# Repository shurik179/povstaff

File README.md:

# POV staff
This repository contains all files related to Persistence of Vision (POV) staff project. A detailed write-up of Version 1 of this project is available on  Instructables at [https://www.instructables.com/Persistence-of-Vision-LED-Staff/](https://www.instructables.com/Persistence-of-Vision-LED-Staff/); you can also find there photos  of the staff in action.

The latest version (as of June 1, 2023) is 4.1. It is documented at
https://povstaff.readthedocs.io

## Structure of this repository  
This repository is organized as follows:

* `docs`: documentation
* `code`: this directory contains the source code for the staff software
* `hardware`:  design files for the custom PCBs used in
  the project, as well as STEP files for the 3d printed components.
* `images`: sample image(s) and  `imagelist.txt` file

## Authors and license
This project was created by Alexander Kirillov <irobotics.store@gmail.com>; it is
based on [earlier work](https://learn.adafruit.com/pov-dotstar-double-staff) of
Phillip Burgess and Erin St Blaine from Adafruit. The project is available under
MIT license; see LICENSE file for details.

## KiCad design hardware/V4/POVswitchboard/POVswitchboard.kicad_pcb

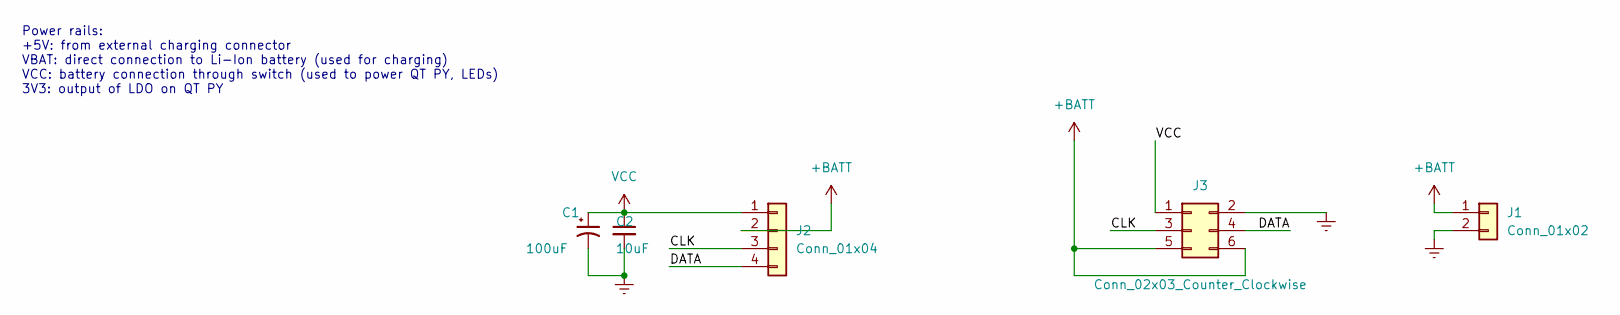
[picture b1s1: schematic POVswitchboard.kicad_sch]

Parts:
C1: 100uF; CP_Radial_D6.3mm_P2.50mm
C2: 10uF; C_0805_2012Metric; LCSC C15850
J1: Conn_01x02; JST_XH_B2B-XH-A_1x02_P2.50mm_Vertical
J2: Conn_01x04; connector-4p-large-nosilk
J3: Conn_02x03_Counter_Clockwise; PinSocket_2x03_P2.54mm_Horizontal

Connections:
+BATT: J1.1, J2.2, J3.5, J3.6
/CLK: J2.3, J3.3
/DATA: J2.4, J3.4
GNDREF: C1.2, C2.2, J1.2, J3.2
VCC: C1.1, C2.1, J2.1, J3.1

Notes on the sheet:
Power rails: +5V: from external charging connector VBAT: direct connection to Li-Ion battery (used for charging) VCC: battery connection through switch (used to power QT PY, LEDs) 3V3: output of LDO on QT PY

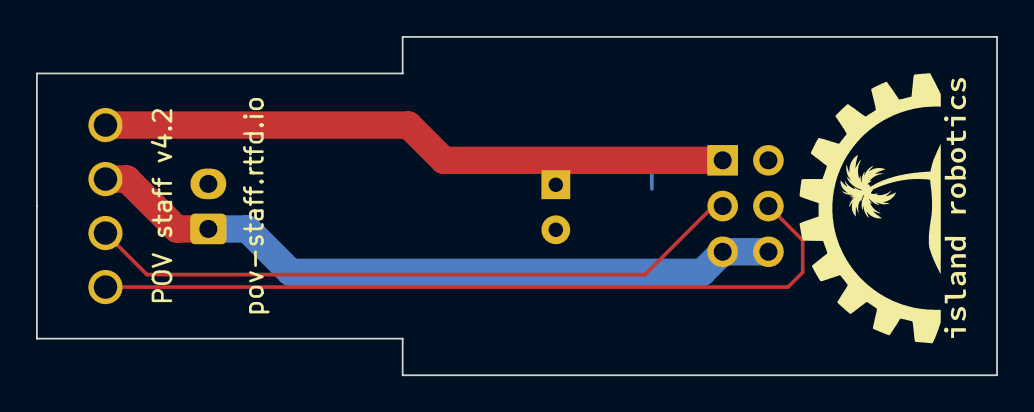
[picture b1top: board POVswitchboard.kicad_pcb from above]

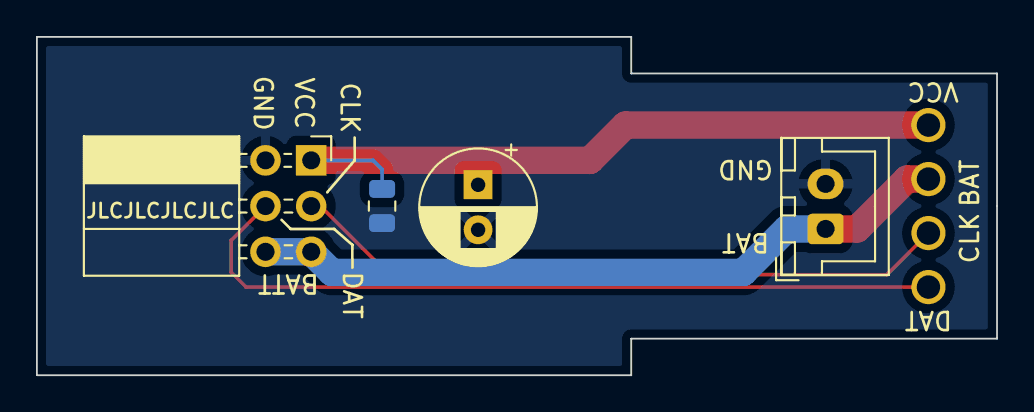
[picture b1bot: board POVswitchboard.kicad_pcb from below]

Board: 2 copper layers, 53.3 x 18.8 mm, 5 parts (4 on the bottom side), 5 nets.

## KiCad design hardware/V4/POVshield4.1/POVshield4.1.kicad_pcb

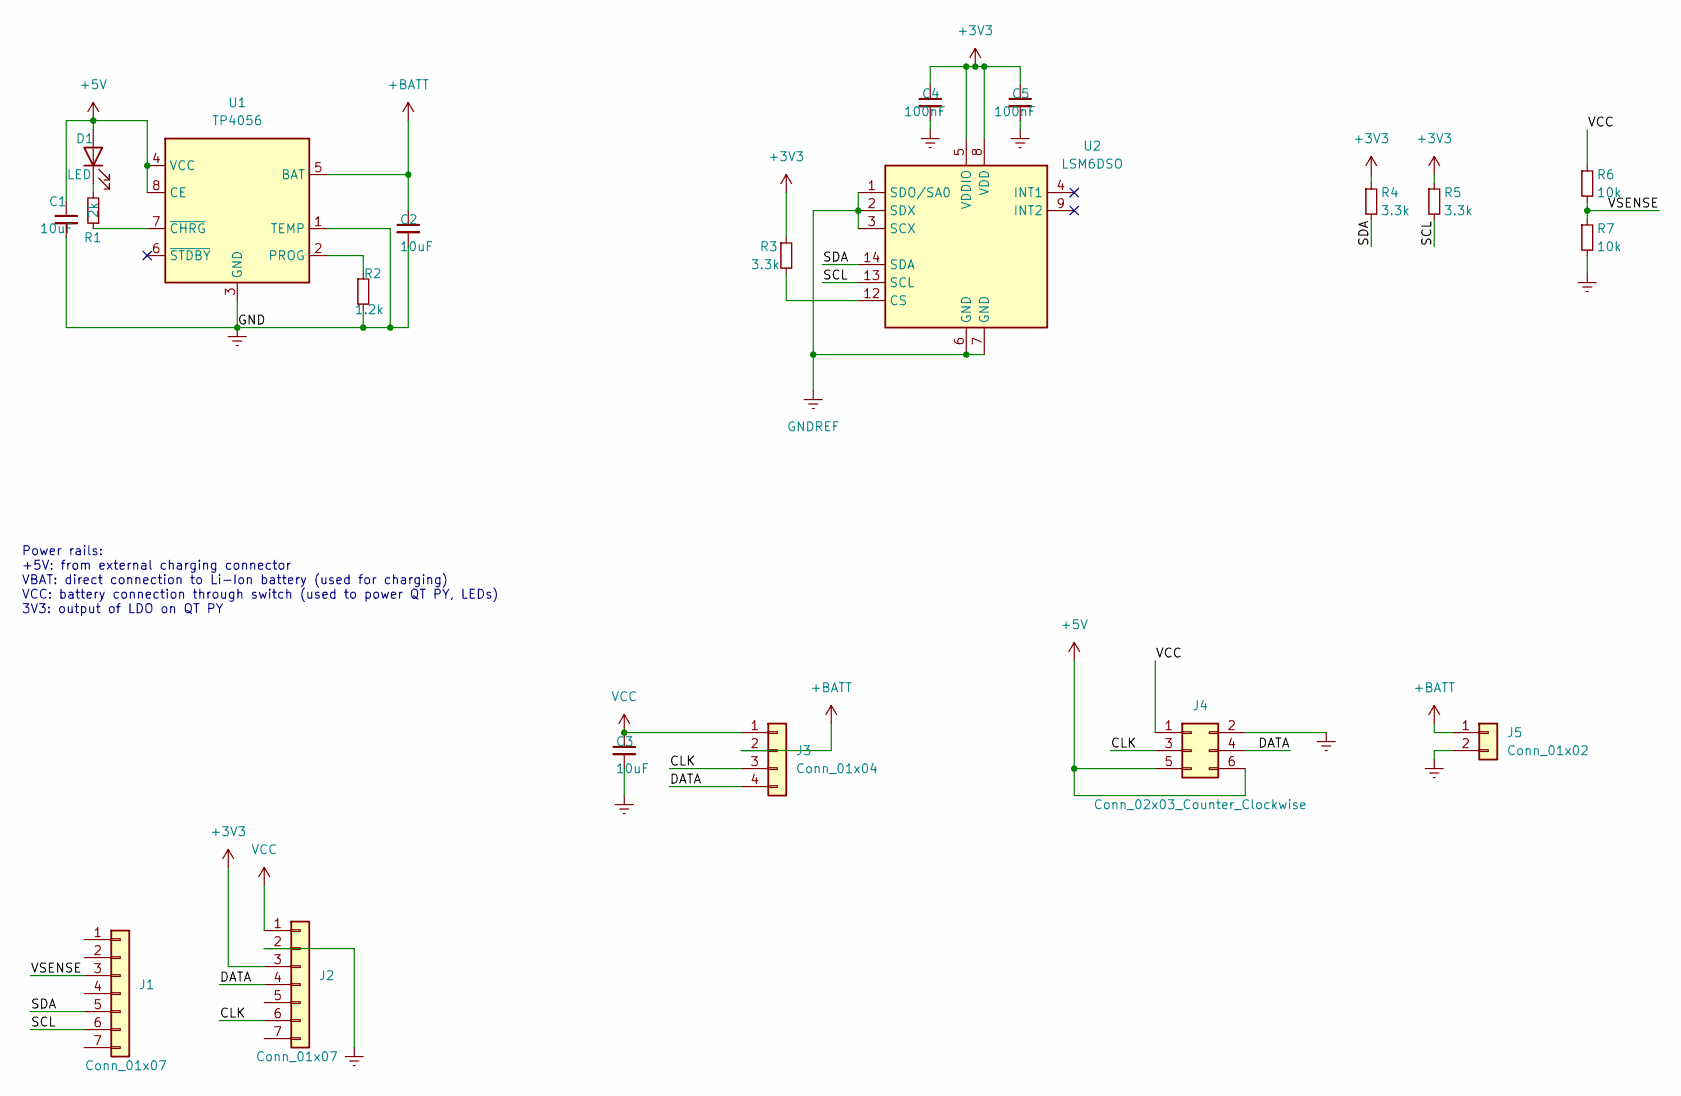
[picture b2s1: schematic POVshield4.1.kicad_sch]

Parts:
C1, C2, C3: 10uF; C_0805_2012Metric; LCSC C15850
C4, C5: 100nF; C_0603_1608Metric; LCSC C14663
D1: LED; LED_0603_1608Metric; LCSC C72038
J1, J2: Conn_01x07; PinSocket_1x07_P2.54mm_Vertical
J3: Conn_01x04; connector-4p-large-nosilk
J4: Conn_02x03_Counter_Clockwise; PinSocket_2x03_P2.54mm_Horizontal
J5: Conn_01x02; JST_XH_B2B-XH-A_1x02_P2.50mm_Vertical
R1: 2k; R_0603_1608Metric; LCSC C22975
R2: 1.2k; R_0603_1608Metric; LCSC C22765
R3, R4, R5: 3.3k; R_0603_1608Metric; LCSC C22978
R6, R7: 10k; R_0603_1608Metric; LCSC C25804
U1: TP4056; HSOP-8-1EP_3.9x4.9mm_P1.27mm_EP2.41x3.1mm_ThermalVias; LCSC C16581
U2: LSM6DSO; Bosch_LGA-14_3x2.5mm_P0.5mm

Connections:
+3V3: C4.1, C5.1, J2.3, R3.1, R4.1, R5.1, U2.5 (VDDIO), U2.8 (VDD)
+5V: C1.1, D1.2 (A), J4.5, J4.6, U1.4 (VCC), U1.8 (CE)
+BATT: C2.1, J3.2, J5.1, U1.5 (BAT)
/CLK: J2.6, J3.3, J4.3
/DATA: J2.4, J3.4, J4.4
/SCL: J1.6, R5.2, U2.13 (SCL)
/SDA: J1.5, R4.2, U2.14 (SDA)
/VSENSE: J1.3, R6.2, R7.1
EP: C1.2, C2.2, C3.2, C4.2, C5.2, J2.2, J4.2, J5.2, R2.2, R7.2, U1.1 (TEMP), U1.3 (GND), U1.9 (EP), U2.1 (SDO/SA0), U2.2 (SDX), U2.3 (SCX), U2.6 (GND), U2.7 (GND)
unnamed: D1.1 (K), R1.2
unnamed: R1.1, U1.7 (~CHRG)
unnamed: R2.1, U1.2 (PROG)
unnamed: R3.2, U2.12 (CS)
VCC: C3.1, J2.1, J3.1, J4.1, R6.1

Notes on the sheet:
Power rails: +5V: from external charging connector VBAT: direct connection to Li-Ion battery (used for charging) VCC: battery connection through switch (used to power QT PY, LEDs) 3V3: output of LDO on QT PY

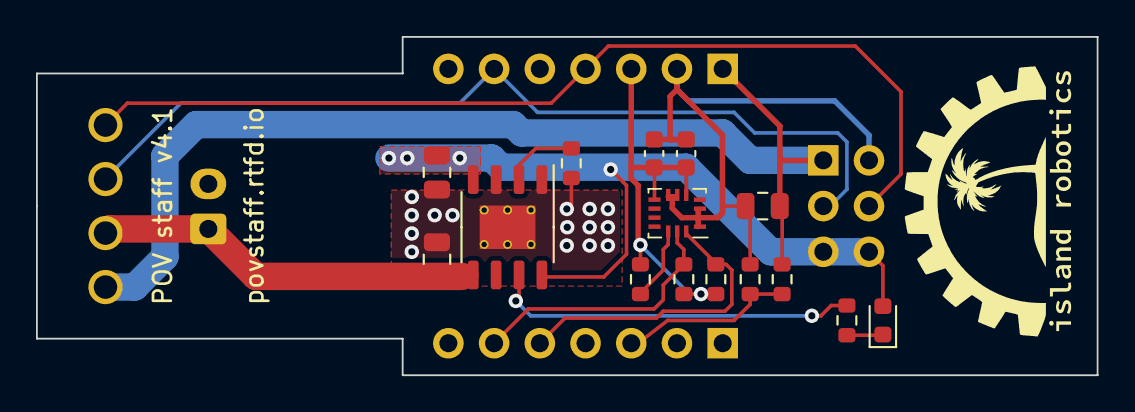
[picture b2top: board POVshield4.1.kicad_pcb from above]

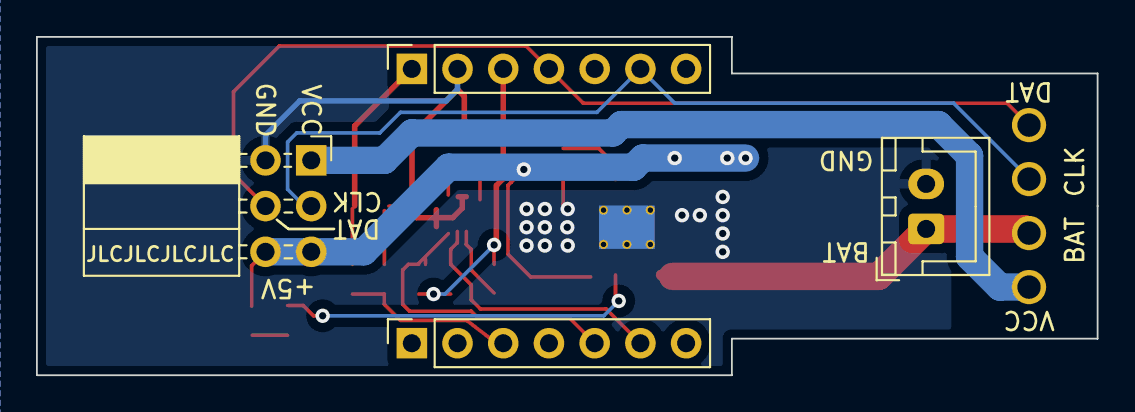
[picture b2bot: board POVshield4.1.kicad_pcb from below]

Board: 2 copper layers, 58.9 x 18.8 mm, 20 parts (4 on the bottom side), 14 nets.

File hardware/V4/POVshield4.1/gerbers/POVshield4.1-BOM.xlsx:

Designator | Footprint | Comment | JLCPCB Part #（optional）
C1,C2,C3 | C_0805_2012Metric | 10uF | C15850
C4,C5 | C_0603_1608Metric | 100nF | C14663
D1 | LED_0603_1608Metric | LED | C72038
R1 | R_0603_1608Metric | 2k | C22975
R2 | R_0603_1608Metric | 1.2k | C22765
R3,R4,R5 | R_0603_1608Metric | 3.3k | C22978
R6,R7 | R_0603_1608Metric | 10k | C25804
U2 | Bosch_LGA-14_3x2.5mm_P0.5mm | LSM6DSO | C2829074
U1 | HSOP-8-1EP_3.9x4.9mm_P1.27mm_EP2.41x3.1mm_ThermalVias | TP4056 | C16581

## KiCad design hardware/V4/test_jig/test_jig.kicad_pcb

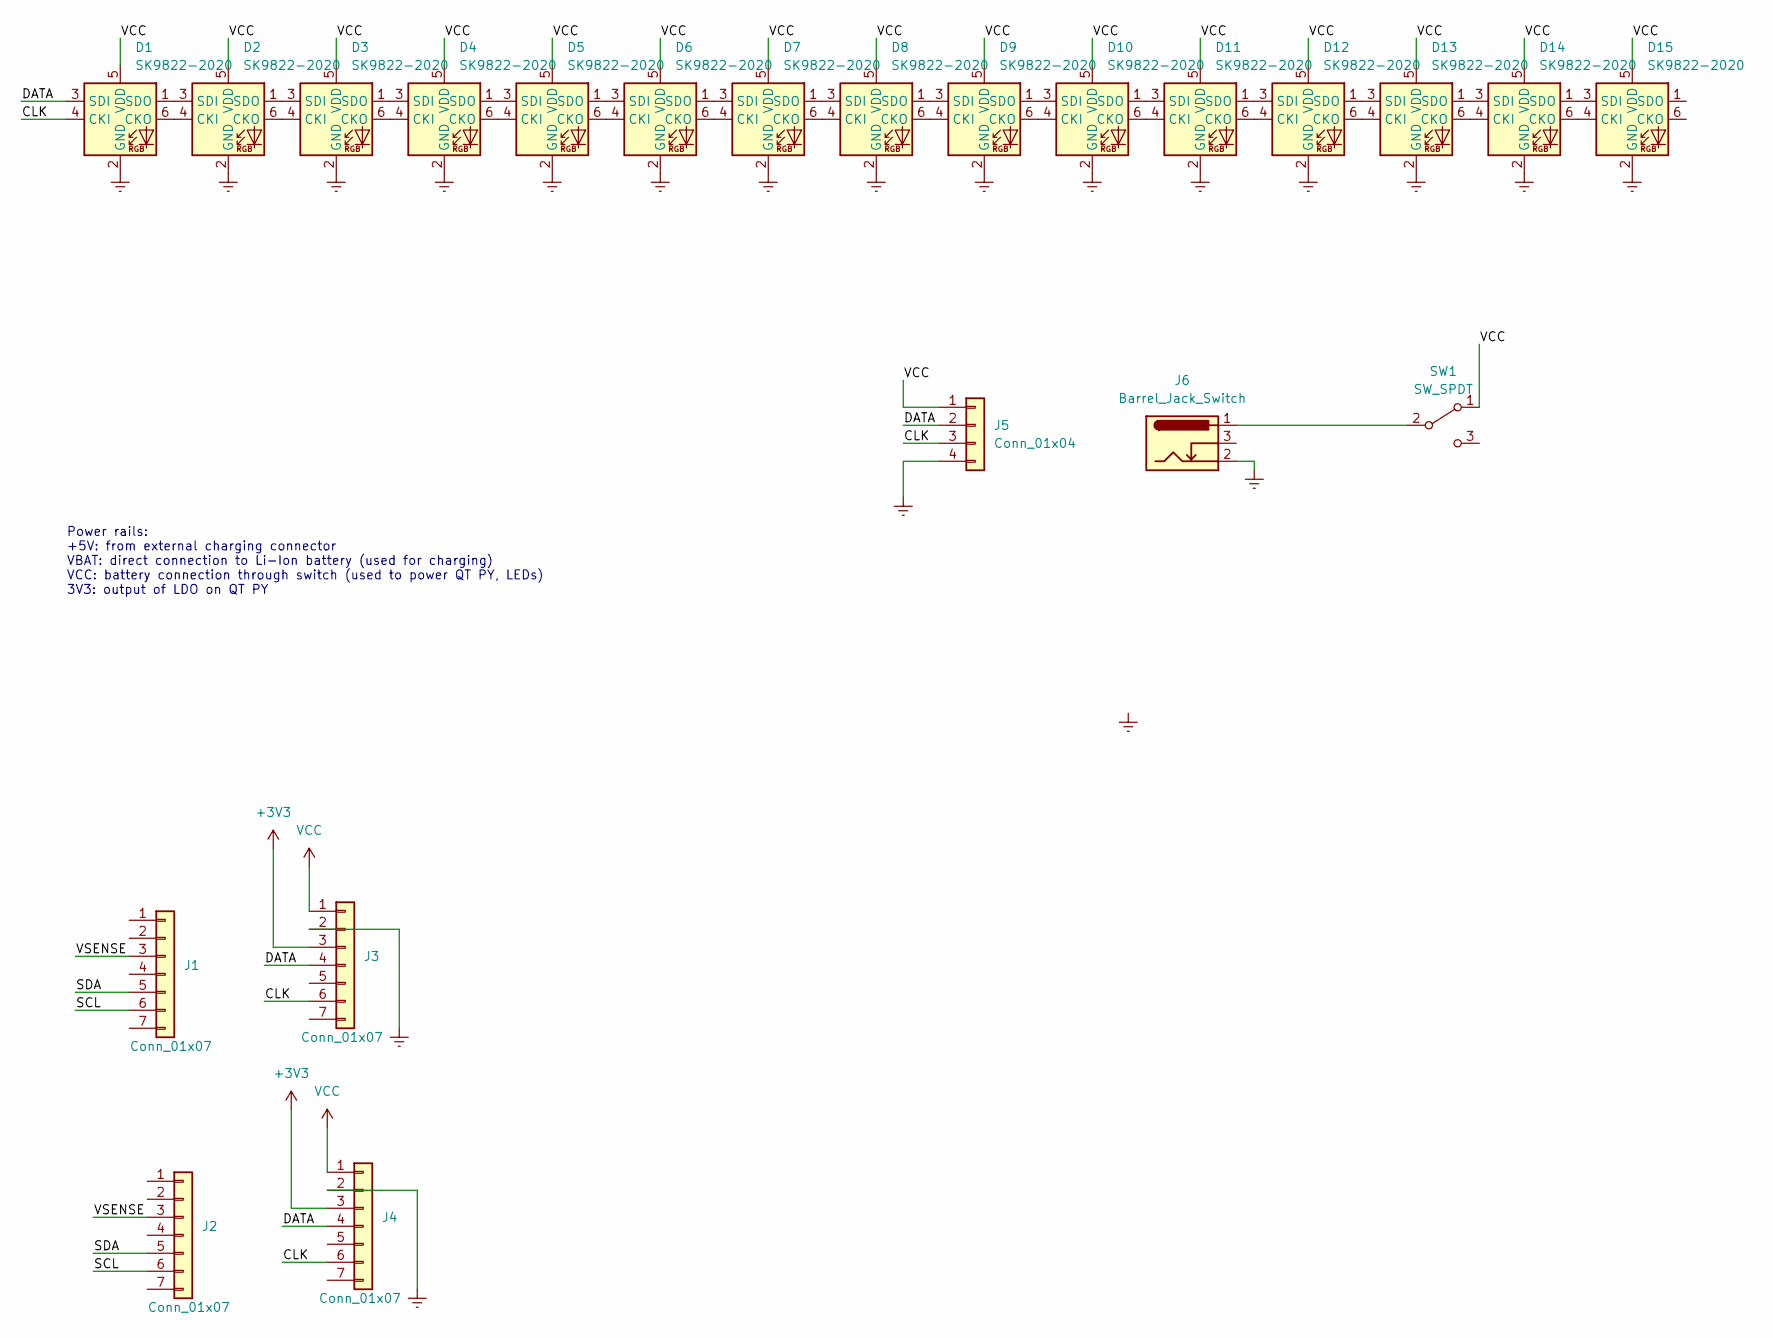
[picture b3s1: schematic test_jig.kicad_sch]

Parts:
D1, D2, D3, D4, D5, D6, D7, D8, D9, D10, D11, D12, D13, D14, D15: SK9822-2020; LED-SK9822-2020
J1, J2, J3, J4: Conn_01x07
J5: Conn_01x04; connector-4p-large-nosilk
J6: Barrel_Jack_Switch; BarrelJack_GCT_DCJ200-10-A_Horizontal
SW1: SW_SPDT; SW_XKB_SS12D10L3

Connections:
+3V3: J3.3, J4.3
/CLK: D1.4 (CKI), J3.6, J4.6, J5.3
/DATA: D1.3 (SDI), J3.4, J4.4, J5.2
/SCL: J1.6, J2.6
/SDA: J1.5, J2.5
/VSENSE: J1.3, J2.3
GNDREF: D1.2 (GND), D2.2 (GND), D3.2 (GND), D4.2 (GND), D5.2 (GND), D6.2 (GND), D7.2 (GND), D8.2 (GND), D9.2 (GND), D10.2 (GND), D11.2 (GND), D12.2 (GND), D13.2 (GND), D14.2 (GND), D15.2 (GND), J3.2, J4.2, J5.4, J6.2
unnamed: D1.1 (SDO), D2.3 (SDI)
unnamed: D1.6 (CKO), D2.4 (CKI)
unnamed: D2.1 (SDO), D3.3 (SDI)
unnamed: D2.6 (CKO), D3.4 (CKI)
unnamed: D3.1 (SDO), D4.3 (SDI)
unnamed: D3.6 (CKO), D4.4 (CKI)
unnamed: D4.1 (SDO), D5.3 (SDI)
unnamed: D4.6 (CKO), D5.4 (CKI)
unnamed: D5.1 (SDO), D6.3 (SDI)
unnamed: D5.6 (CKO), D6.4 (CKI)
unnamed: D6.1 (SDO), D7.3 (SDI)
unnamed: D6.6 (CKO), D7.4 (CKI)
unnamed: D7.1 (SDO), D8.3 (SDI)
unnamed: D7.6 (CKO), D8.4 (CKI)
unnamed: D8.1 (SDO), D9.3 (SDI)
unnamed: D8.6 (CKO), D9.4 (CKI)
unnamed: D10.1 (SDO), D11.3 (SDI)
unnamed: D9.1 (SDO), D10.3 (SDI)
unnamed: D9.6 (CKO), D10.4 (CKI)
unnamed: D10.6 (CKO), D11.4 (CKI)
unnamed: D11.1 (SDO), D12.3 (SDI)
unnamed: D11.6 (CKO), D12.4 (CKI)
unnamed: D12.1 (SDO), D13.3 (SDI)
unnamed: D12.6 (CKO), D13.4 (CKI)
unnamed: D13.1 (SDO), D14.3 (SDI)
unnamed: D13.6 (CKO), D14.4 (CKI)
unnamed: D14.1 (SDO), D15.3 (SDI)
unnamed: D14.6 (CKO), D15.4 (CKI)
unnamed: J6.1, SW1.2 (B)
VCC: D1.5 (VDD), D2.5 (VDD), D3.5 (VDD), D4.5 (VDD), D5.5 (VDD), D6.5 (VDD), D7.5 (VDD), D8.5 (VDD), D9.5 (VDD), D10.5 (VDD), D11.5 (VDD), D12.5 (VDD), D13.5 (VDD), D14.5 (VDD), D15.5 (VDD), J3.1, J4.1, J5.1, SW1.1 (A)

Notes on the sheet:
Power rails: +5V: from external charging connector VBAT: direct connection to Li-Ion battery (used for charging) VCC: battery connection through switch (used to power QT PY, LEDs) 3V3: output of LDO on QT PY

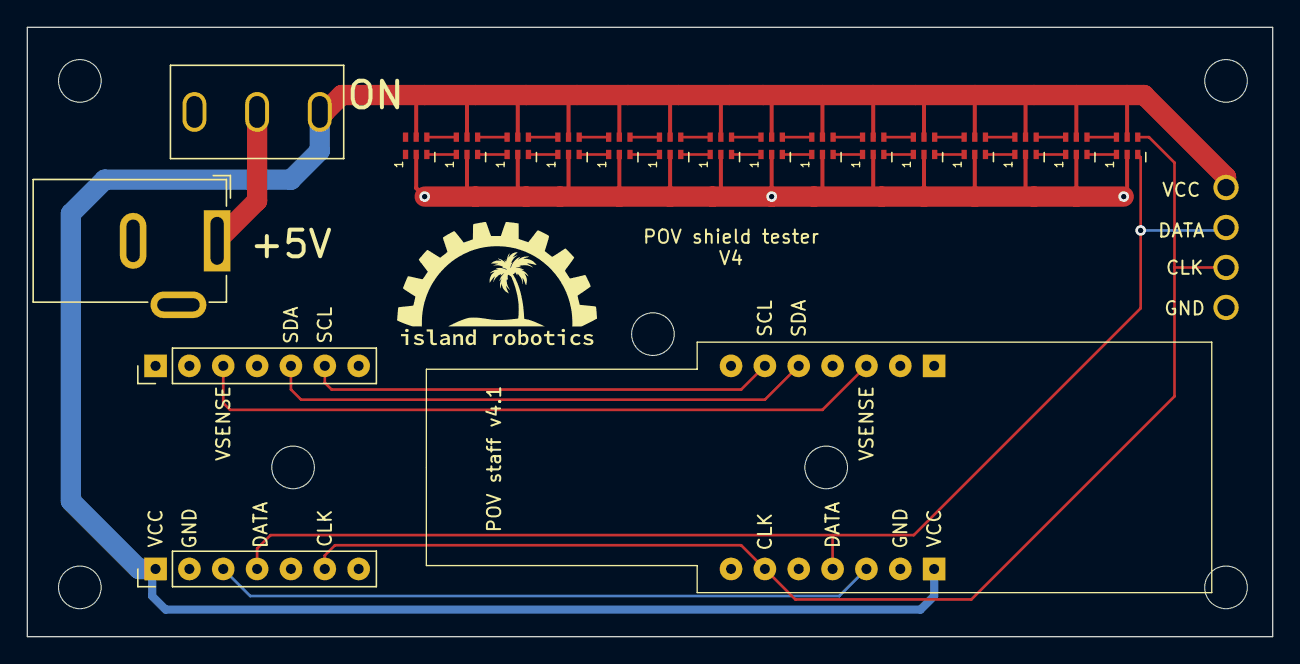
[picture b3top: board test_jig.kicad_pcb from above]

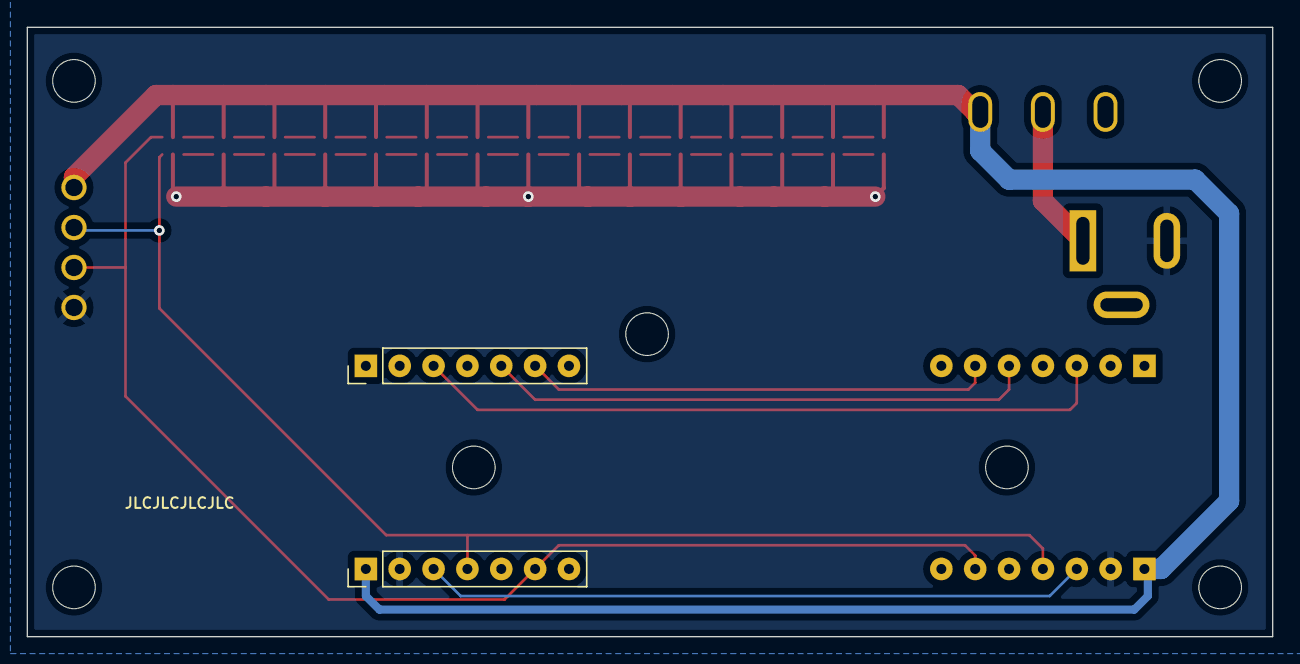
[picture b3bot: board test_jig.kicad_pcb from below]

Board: 2 copper layers, 93.4 x 45.7 mm, 22 parts (2 on the bottom side), 37 nets.

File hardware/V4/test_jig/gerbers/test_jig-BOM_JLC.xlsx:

Comment | Designator | Footprint | JLCPCB Part #（optional）
SK9822-EC2020 LED | D1,D2,D3,D4,D5,D6,D7,D8,D9,D10,D11,D12,D13,D14,D15 | 2020 | C2909059

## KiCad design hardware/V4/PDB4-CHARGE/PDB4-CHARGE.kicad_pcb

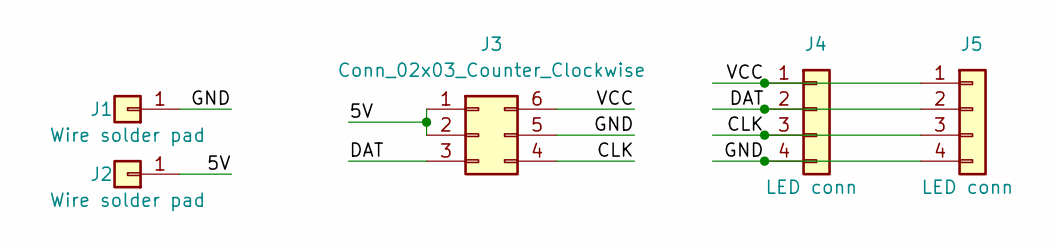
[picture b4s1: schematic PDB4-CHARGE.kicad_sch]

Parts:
J1: Wire solder pad
J2: Wire solder pad; TestPoint_Plated_Hole_D2.0mm
J3: Conn_02x03_Counter_Clockwise; PinHeader_2x03_P2.54mm_Vertical
J4, J5: LED conn; connector-4p-generic-nosilk

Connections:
/5V: J2.1, J3.1, J3.2
/CLK: J3.4, J4.3, J5.3
/DAT: J3.3, J4.2, J5.2
/GND: J1.1, J3.5, J4.4, J5.4
/VCC: J3.6, J4.1, J5.1

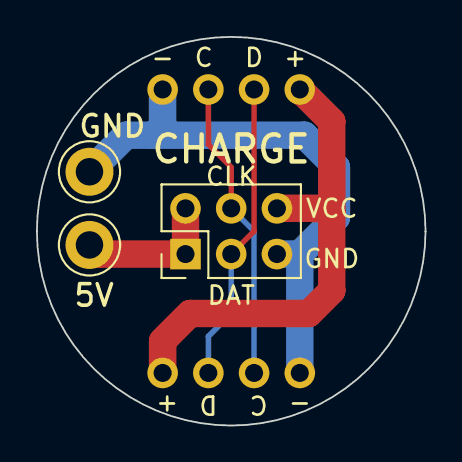
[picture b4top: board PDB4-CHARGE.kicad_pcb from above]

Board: 2 copper layers, 21.6 x 21.6 mm, 5 parts (0 on the bottom side), 5 nets.

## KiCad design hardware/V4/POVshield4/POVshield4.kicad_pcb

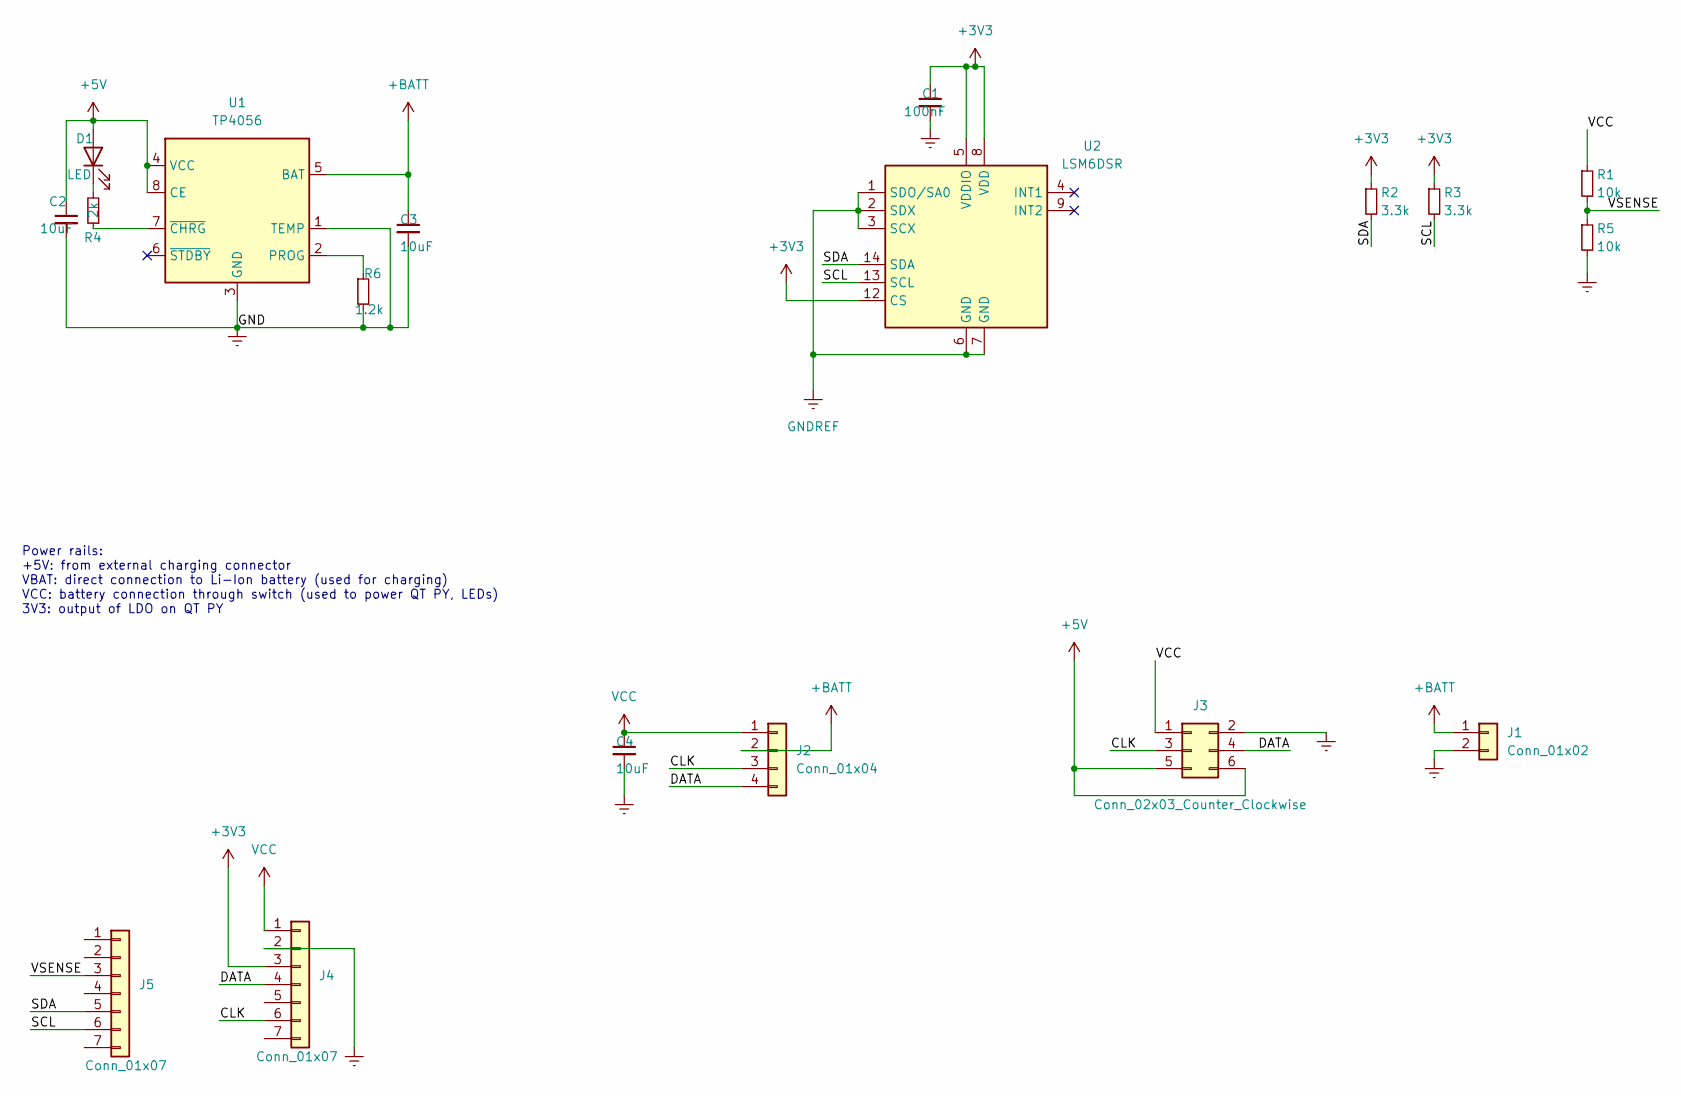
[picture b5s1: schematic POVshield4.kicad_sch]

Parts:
C1: 100nF; C_0603_1608Metric; LCSC C14663
C2, C3, C4: 10uF; C_0805_2012Metric; LCSC C15850
D1: LED; LED_0603_1608Metric; LCSC C72038
J1: Conn_01x02; JST_XH_B2B-XH-A_1x02_P2.50mm_Vertical
J2: Conn_01x04; connector-4p-large-nosilk
J3: Conn_02x03_Counter_Clockwise; PinSocket_2x03_P2.54mm_Horizontal
J4, J5: Conn_01x07; PinSocket_1x07_P2.54mm_Vertical
R1, R5: 10k; R_0603_1608Metric; LCSC C25804
R2, R3: 3.3k; R_0603_1608Metric; LCSC C22978
R4: 2k; R_0603_1608Metric; LCSC C22975
R6: 1.2k; R_0603_1608Metric; LCSC C22765
U1: TP4056; HSOP-8-1EP_3.9x4.9mm_P1.27mm_EP2.41x3.1mm_ThermalVias; LCSC C16581
U2: LSM6DSR; Bosch_LGA-14_3x2.5mm_P0.5mm

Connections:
+3V3: C1.1, J4.3, R2.1, R3.1, U2.5 (VDDIO), U2.8 (VDD), U2.12 (CS)
+5V: C2.1, D1.2 (A), J3.5, J3.6, U1.4 (VCC), U1.8 (CE)
+BATT: C3.1, J1.1, J2.2, U1.5 (BAT)
/CLK: J2.3, J3.3, J4.6
/DATA: J2.4, J3.4, J4.4
/SCL: J5.6, R3.2, U2.13 (SCL)
/SDA: J5.5, R2.2, U2.14 (SDA)
/VSENSE: J5.3, R1.2, R5.1
EP: C1.2, C2.2, C3.2, C4.2, J1.2, J3.2, J4.2, R5.2, R6.2, U1.1 (TEMP), U1.3 (GND), U1.9 (EP), U2.1 (SDO/SA0), U2.2 (SDX), U2.3 (SCX), U2.6 (GND), U2.7 (GND)
unnamed: D1.1 (K), R4.2
unnamed: R4.1, U1.7 (~CHRG)
unnamed: R6.1, U1.2 (PROG)
VCC: C4.1, J2.1, J3.1, J4.1, R1.1

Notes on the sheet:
Power rails: +5V: from external charging connector VBAT: direct connection to Li-Ion battery (used for charging) VCC: battery connection through switch (used to power QT PY, LEDs) 3V3: output of LDO on QT PY

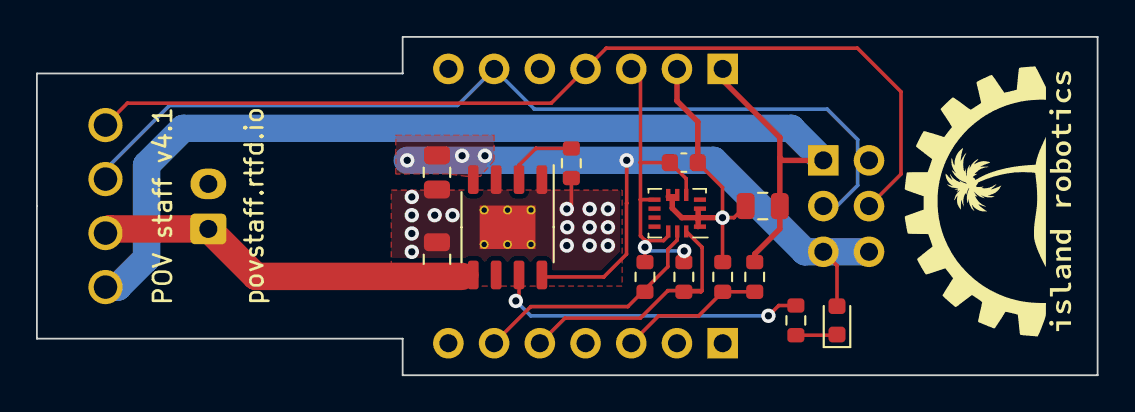
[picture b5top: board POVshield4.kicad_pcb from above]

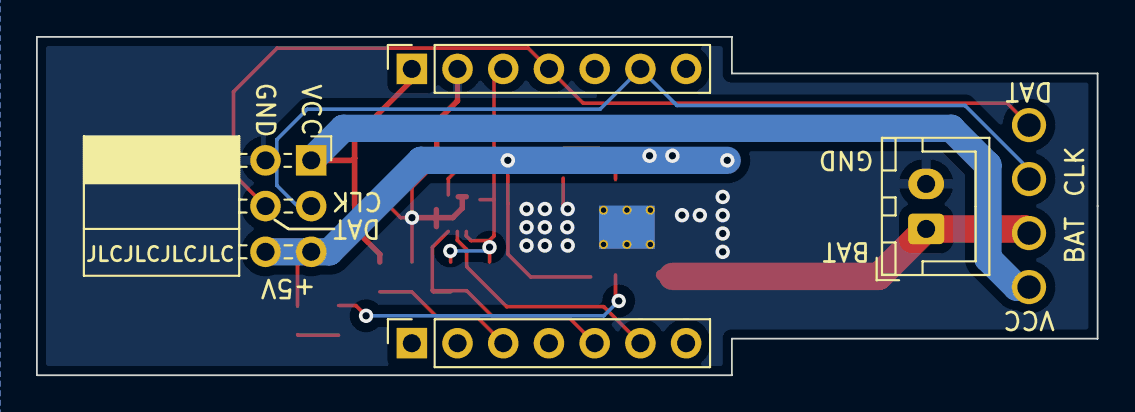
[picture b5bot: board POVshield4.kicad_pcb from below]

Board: 2 copper layers, 58.9 x 18.8 mm, 18 parts (4 on the bottom side), 13 nets.

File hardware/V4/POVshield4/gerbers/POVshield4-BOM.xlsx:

Designator | Footprint | Comment | JLCPCB Part #（optional）
C3,C2,C4 | C_0805_2012Metric | 10uF | C15850
R4 | R_0603_1608Metric | 2k | C22975
D1 | LED_0603_1608Metric | LED | C72038
R1,R5 | R_0603_1608Metric | 10k | C25804
U2 | Bosch_LGA-14_3x2.5mm_P0.5mm | LSM6DSR | C784817
U1 | HSOP-8-1EP_3.9x4.9mm_P1.27mm_EP2.41x3.1mm_ThermalVias | TP4056 | C16581
R6 | R_0603_1608Metric | 1.2k | C22765
R2,R3 | R_0603_1608Metric | 3.3k | C22978
C1 | C_0603_1608Metric | 100nF | C14663

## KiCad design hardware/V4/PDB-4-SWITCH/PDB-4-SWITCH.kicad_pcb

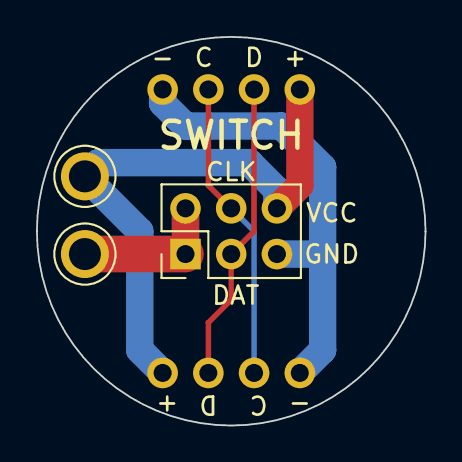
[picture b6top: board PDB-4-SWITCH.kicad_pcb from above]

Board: 2 copper layers, 21.6 x 21.6 mm, 5 parts (0 on the bottom side), 5 nets.

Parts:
J1, J2: LED conn; connector-4p-generic-nosilk
J3, J4: Wire solder pad; TestPoint_Plated_Hole_D2.0mm
J5: Conn_02x03_Counter_Clockwise; PinHeader_2x03_P2.54mm_Vertical

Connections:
/CLK: J1.3, J2.3, J5.4
/DAT: J1.2, J2.2, J5.3
/GND: J1.4, J2.4, J5.5
/VBAT: J4.1, J5.1, J5.2
/VCC: J1.1, J2.1, J3.1, J5.6

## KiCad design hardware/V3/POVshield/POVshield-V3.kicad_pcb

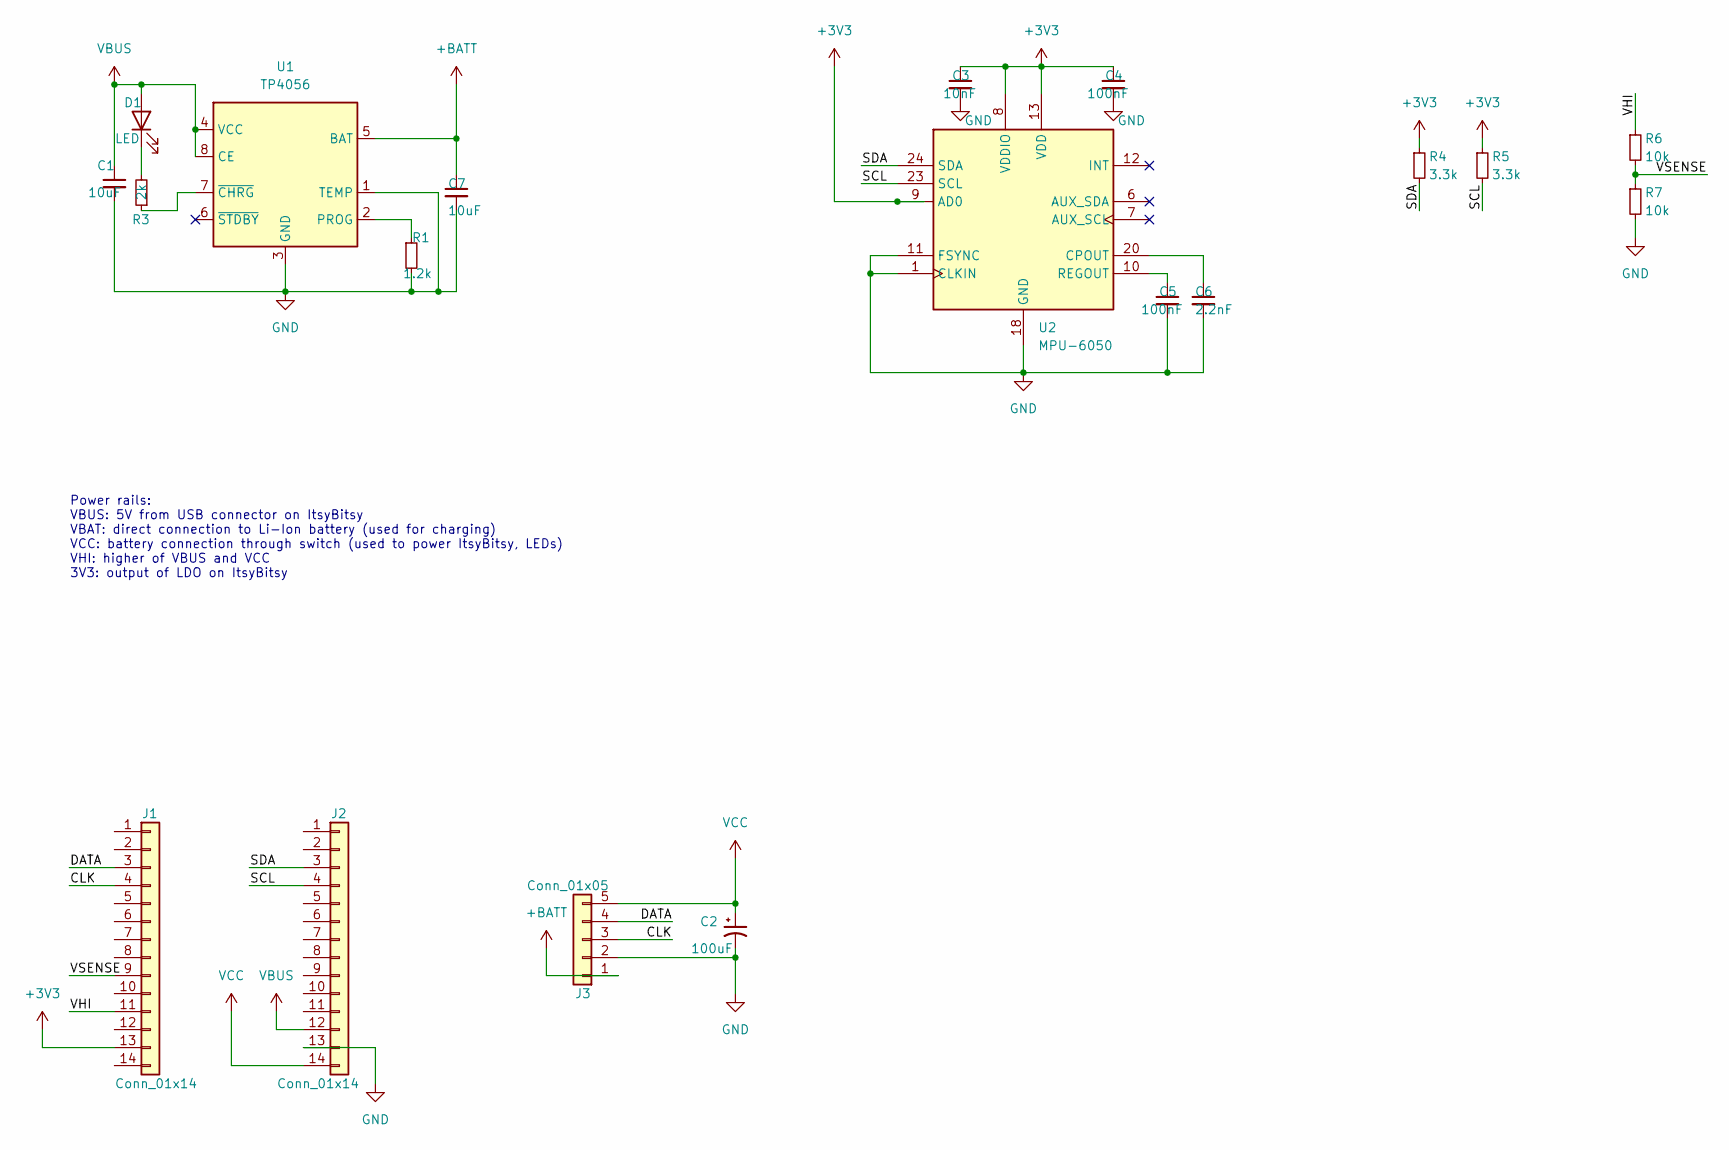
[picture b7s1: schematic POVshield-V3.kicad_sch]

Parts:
C1, C7: 10uF; C_0805_2012Metric; LCSC C15850
C2: 100uF; CP_Radial_D6.3mm_P2.50mm; LCSC C43804
C3: 10nF; C_0603_1608Metric; LCSC C57112
C4, C5: 100nF; C_0603_1608Metric; LCSC C14663
C6: 2.2nF; C_0603_1608Metric; LCSC C1604
D1: LED; LED_0603_1608Metric; LCSC C72038
J1, J2: Conn_01x14; PinSocket_1x14_P2.54mm_Vertical
J3: Conn_01x05; JST_XH_B5B-XH-A_1x05_P2.50mm_Vertical
R1: 1.2k; R_0603_1608Metric; LCSC C22765
R3: 2k; R_0603_1608Metric; LCSC C22975
R4, R5: 3.3k; R_0603_1608Metric; LCSC C22978
R6, R7: 10k; R_0603_1608Metric; LCSC C25804
U1: TP4056; HSOP-8-1EP_3.9x4.9mm_P1.27mm_EP2.41x3.1mm_ThermalVias; LCSC C16581
U2: MPU-6050; InvenSense_QFN-24_4x4mm_P0.5mm; LCSC C24112

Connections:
+3V3: C3.1, C4.1, J1.13, R4.1, R5.1, U2.8 (VDDIO), U2.9 (AD0), U2.13 (VDD)
+BATT: C7.1, J3.1, U1.5 (BAT)
/CLK: J1.4, J3.3
/DATA: J1.3, J3.4
/SCL: J2.4, R5.2, U2.23 (SCL)
/SDA: J2.3, R4.2, U2.24 (SDA)
/VHI: J1.11, R6.1
/VSENSE: J1.9, R6.2, R7.1
GND: C1.2, C2.2, C3.2, C4.2, C5.2, C6.2, C7.2, J2.13, J3.2, R1.2, R7.2, U1.1 (TEMP), U1.3 (GND), U1.9 (EP), U2.1 (CLKIN), U2.11 (FSYNC), U2.18 (GND)
unnamed: C5.1, U2.10 (REGOUT)
unnamed: C6.1, U2.20 (CPOUT)
unnamed: D1.1 (K), R3.2
unnamed: R1.1, U1.2 (PROG)
unnamed: R3.1, U1.7 (~CHRG)
VBUS: C1.1, D1.2 (A), J2.12, U1.4 (VCC), U1.8 (CE)
VCC: C2.1, J2.14, J3.5

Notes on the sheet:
Power rails: VBUS: 5V from USB connector on ItsyBitsy VBAT: direct connection to Li-Ion battery (used for charging) VCC: battery connection through switch (used to power ItsyBitsy, LEDs) VHI: higher of VBUS and VCC 3V3: output of LDO on ItsyBitsy

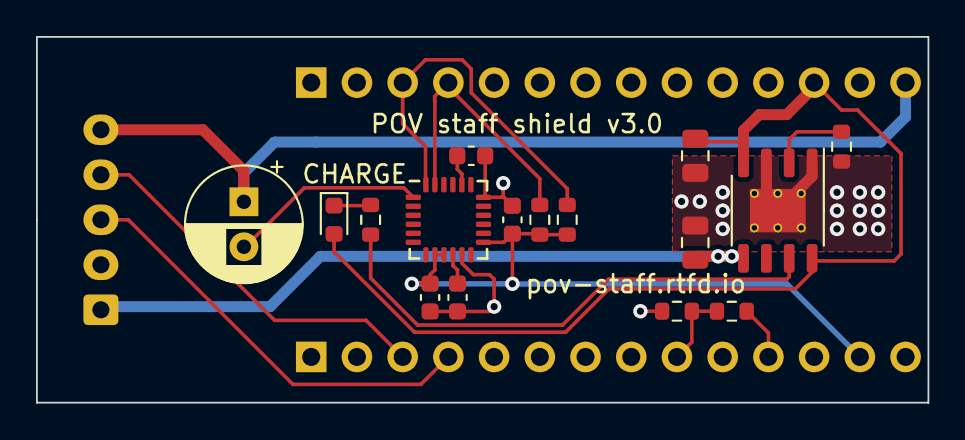
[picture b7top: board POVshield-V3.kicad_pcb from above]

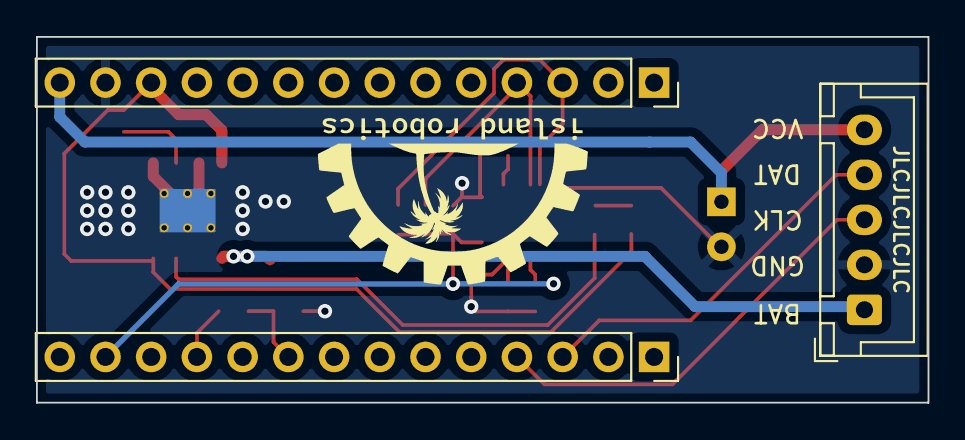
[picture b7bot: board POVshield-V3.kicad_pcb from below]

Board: 2 copper layers, 49.5 x 20.3 mm, 19 parts (3 on the bottom side), 16 nets.

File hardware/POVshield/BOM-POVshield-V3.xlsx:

Component | Description | Part Number | References | Value | Footprint | Qnty | LCSC
1 | SMD capacitor, 10uF, 0805 |  | C1, C7, | 10uF | 0805 | 2 | C15850
2 | Electrolytic capacitor, 100uF |  | C2, | 100uF | CP_Radial_D6.3mm_P2.50mm | 1 | C43804
3 | SMD capacitor, 10nF, 0603 |  | C3, | 10nF | 0603 | 1 | C57112
4 | SMD capacitor, 100nF, 0603 |  | C4, C5, | 100nF | 0603 | 2 | C14663
5 | SMD capacitor, 2.2nF, 0603 |  | C6, | 2.2nF | 0603 | 1 | C1604
6 | LED, yellow, 0603 |  | D1, |  | 0603 | 1 | C72038
7 | SMD resistor, 0603 |  | R1, | 1.2k | 0603 | 1 | C22765
8 | SMD resistor, 0603 |  | R3, | 2k | 0603 | 1 | C22975
9 | SMD resistor, 0603 |  | R4, R5, | 3.3k | 0603 | 2 | C22978
10 | SMD resistor, 0603 |  | R6, R7, | 10k | 0603 | 2 | C25804
11 | 1A, Single-Input, SingleCell Li-Ion and Li-Pol BatteryCharger, SO-8 | TP4056-42 | U1, | TP4056 | SOP-8 | 1 | C16581
12 | InvenSense 6-Axis Motion Sensor, Gyroscope, Accelerometer, I2C | MPU-6050 | U2, | MPU-6050 | QFN-24 | 1 | C24112

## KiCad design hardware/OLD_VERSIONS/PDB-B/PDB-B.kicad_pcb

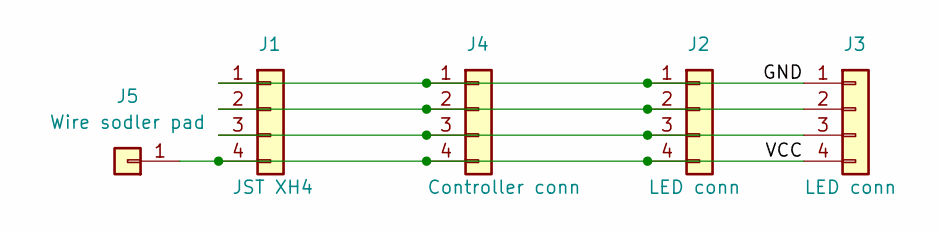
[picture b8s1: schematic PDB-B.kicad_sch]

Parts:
J1: JST XH4; JST_XH_B4B-XH-A_1x04_P2.50mm_Vertical
J2, J3: LED conn; connector-4p-generic-nosilk
J4: Controller conn; connector-4p-generic-nosilk
J5: Wire sodler pad; TestPoint_Plated_Hole_D2.0mm

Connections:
/GND: J1.1, J2.1, J3.1, J4.1
/VCC: J1.4, J2.4, J3.4, J4.4, J5.1
unnamed: J1.2, J2.2, J3.2, J4.2
unnamed: J1.3, J2.3, J3.3, J4.3

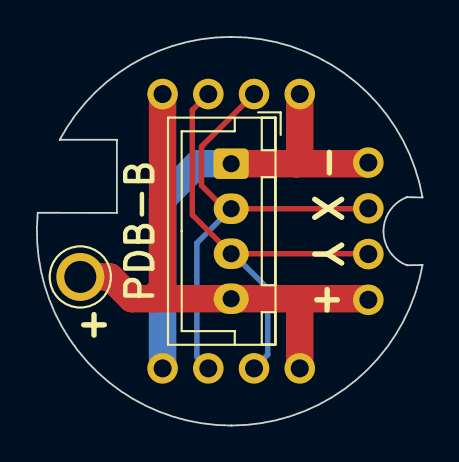
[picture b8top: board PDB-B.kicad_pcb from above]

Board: 2 copper layers, 21.4 x 21.6 mm, 5 parts (0 on the bottom side), 4 nets.

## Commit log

2020-10-16 Create LICENSE
2020-10-16 Initial commit of code and board design
2020-10-17 docs update
2020-10-21 code update; hardware directory update
2020-10-21 docs update - image orientation
2020-10-21 docs update - code README
2020-10-23 fixing bug in povstaff logic
2020-11-05 added image durations imagelist file
2020-11-05 Updated docs
2020-11-05 fixing minor typos
2020-11-05 added binaries
2020-11-06 release 1.0
2020-11-08 added formatter binary
2020-12-05 updated docs; spacer model
2020-12-05 Fixing the user guide
2021-02-27 updating gerbers
2021-12-02 added function to disable ItsyBitsy DotStar while show mode is active
2021-12-02 move images
2022-01-21 Added PDF of power distribution brd
2022-02-26 starting update for 2022 version
2022-03-07 starting work on docs
2022-03-08 docs updtae
2022-03-14 new switch spacer
2022-03-15 docs updating
2022-03-16 new photos for docs
2022-03-17 README updates
2022-03-21 adding PDB3.1; docs update
2022-03-26 fixing the bug with empty duration
2022-03-29 fix code to work with ItsyBitsy nRF52840
2022-03-31 docs updates
2022-04-01 minor doc fixes
2022-04-01 photos update
2022-04-03 created .gitattributes
2022-04-03 minor docs update
2022-04-03 annotated photo
2022-04-04 new version of spacer
2022-04-04 updating for version 3.1
2022-04-04 fixed file extension for controller wire-1a
2022-04-04 adding annotations to images
2022-04-04 final touches
2022-04-05 minor doc updates
2022-10-11 Updating for version 3.2
2022-10-13 updating kit content
2023-04-24 Version 4 - initial commit
2023-04-24 V4 cleanup
2023-04-24 hardware directory cleanup
2023-04-24 updating docs for v4
2023-04-24 docs - images update
2023-04-26 docs and 3d printed update
2023-04-26 docs cleanup
2023-05-12 new images for docs
2023-05-13 docs fix
2023-05-14 final assembly docs update
2023-05-14 docs minor fixes
2023-05-14 docs - image update
2023-05-14 typo fix
2023-05-14 software update
2023-05-16 dowel length fix
2023-05-16 docs work
2023-05-16 new photo for the docs
2023-05-18 added washers to bag F
2023-05-18 fixed copyright year
2023-05-19 minor docs updates
2023-06-01 V4 (#2)
    * Version 4 - initial commit
    * V4 cleanup
    * Update README.md
    * hardware directory cleanup
    * updating docs for v4
    * docs - images update
2023-06-01 new photos
2023-06-14 added handout
2023-07-03 minor update of 3d printed components
2023-10-24 minor changes
2023-10-24 readthedocs build system update
2024-01-02 updated charger spacer
2024-05-03 minor hardware updates
